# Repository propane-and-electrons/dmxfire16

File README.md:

dmxfire16
---------

The dmxfire16 is an Arduino-compatible 16 channel solid state relay board with built-in RS-485 serial. It is the wired version of the [wifire16](https://github.com/propane-and-electrons/wifire16) - much more information on the SSR side of the board is available there.

The RS-485 connection is DMX512 compatible with any number of Arduino libraries, so the dmxfire16 can be used to control LED strip lighting or flame effects with commercial off-the-shelf lighting controllers.

### Feature Summary

* Arduino compatible
  * Use "Duemilanove or Diecimila" as the Board in the Arduino IDE
* Programmable via 6-pin FTDI header or 6-pin ICSP header
* 16 DC load channels switched via MOSFET
* RS-485 support (DMX512 compatible) via 8P8C connectors
* Termination resistor and jumper for serial connection
* All ATMega I/O pins are broken out on the board
* DC load power is optoisolated from the control system power
* Power connectors use 5mm screw terminals or Anderson Powerpole connectors
* Load power status is reported to the microcontroller via an optoisolated input pin
* Output power channels are controlled with a TLC5940 constant current driver that works like a shift register
* Each output channel has a status LED for easy debugging
* TLC5940 control lines are broken out to input/output headers, so boards can be chained without additional control systems

### Documents

* [Schematic](docs/dmxfire16-schematic.pdf)
* [Bill of Materials](docs/dmxfire16-BOM.csv)

### DMX Details

* The [DMXSerial](http://www.mathertel.de/Arduino/DMXSerial.aspx) library can be used.
* **A** from the MAX-485 is positive signal, and goes to RJ-45 pin 1 / XLR pin 3.
* **B** from the MAX-485 is negative signal (aka signal invert), and goes to RJ-45 pin 2 / XLR pin 2.
* Many receivers implement `A-B` in hardware, so if these pins are swapped DMX _is unlikely to work_.

To send DMX data, `CTRLDE` (mapped to Arduino digital pin 6) must be set high:

```
  pinMode(6, OUTPUT);
  digitalWrite(6, HIGH);
```

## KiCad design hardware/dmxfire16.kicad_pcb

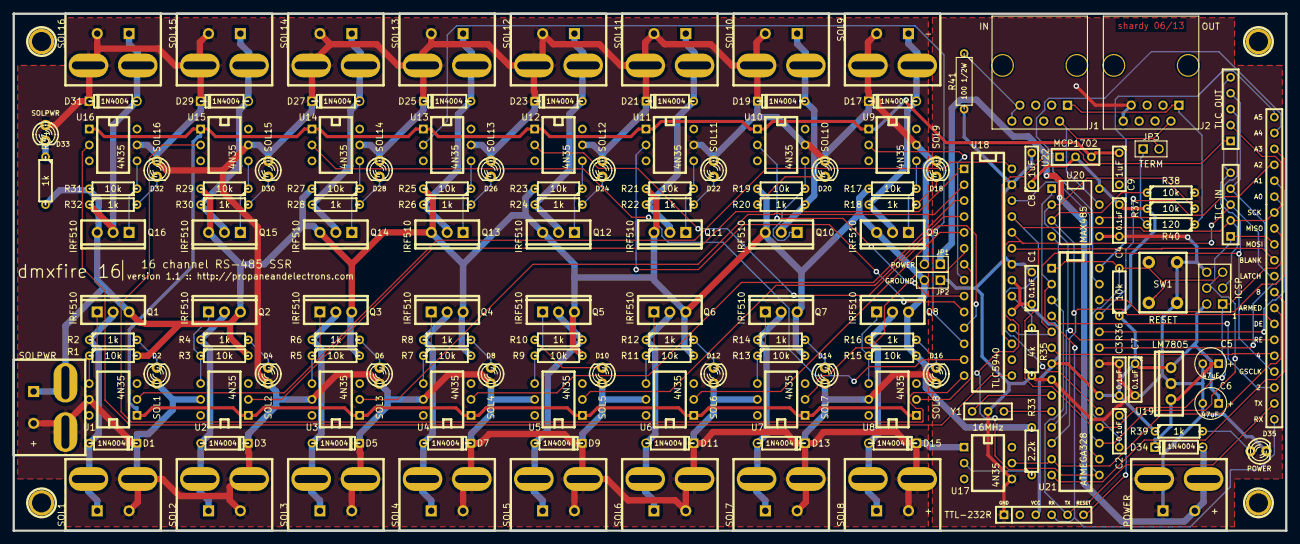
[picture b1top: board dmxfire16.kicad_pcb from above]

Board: 2 copper layers, 203.2 x 82.5 mm, 159 parts (0 on the bottom side), 104 nets.

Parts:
C1, C2, C3, C4, C7: 0.1uF; C2
C5, C6: 47uF; C1V5
C8, C9: 1uF; C2
D1, D3, D5, D7, D9, D11, D13, D15, D17, D19, D21, D23, D25, D27, D29, D31, D34: 1N4004; D3
D2: SOL1; LED-3MM
D4: SOL2; LED-3MM
D6: SOL3; LED-3MM
D8: SOL4; LED-3MM
D10: SOL5; LED-3MM
D12: SOL6; LED-3MM
D14: SOL7; LED-3MM
D16: SOL8; LED-3MM
D18: SOL9; LED-3MM
D20: SOL10; LED-3MM
D22: SOL11; LED-3MM
D24: SOL12; LED-3MM
D26: SOL13; LED-3MM
D28: SOL14; LED-3MM
D30: SOL15; LED-3MM
D32: SOL16; LED-3MM
D33: SOLPWR; LED-3MM
D35: POWER; LED-3MM
H1, H2, H3, H4: SCREWHOLE; 1pin
J1: IN; RJ45_8
J2: OUT; RJ45_8
JP1: POWER; PIN_ARRAY_2X1
JP2: GROUND; PIN_ARRAY_2X1
JP3: TERM; PIN_ARRAY_2X1
P1: SOL1; PP-2H-5MMSCREWTERM
P2: SOL2; PP-2H-5MMSCREWTERM
P3: SOL3; PP-2H-5MMSCREWTERM
P4: SOL4; PP-2H-5MMSCREWTERM
P5: SOL5; PP-2H-5MMSCREWTERM
P6: SOL6; PP-2H-5MMSCREWTERM
P7: SOL7; PP-2H-5MMSCREWTERM
P8: SOL8; PP-2H-5MMSCREWTERM
P9: SOL9; PP-2H-5MMSCREWTERM
P10: SOL10; PP-2H-5MMSCREWTERM
P11: SOL11; PP-2H-5MMSCREWTERM
P12: SOL12; PP-2H-5MMSCREWTERM
P13: SOL13; PP-2H-5MMSCREWTERM
P14: SOL14; PP-2H-5MMSCREWTERM
P15: SOL15; PP-2H-5MMSCREWTERM
P16: SOL16; PP-2H-5MMSCREWTERM
P17: SOLPWR; PP-2H-5MMSCREWTERM
P18: TLC IN; SIL-5
P19: TLC OUT; SIL-5
P20: TTL-232R; SIL-6
P21: ICSP; pin_array_3x2
P22: PORTC; SIL-6
P23: PORTD; SIL-8
P24: PORTB; SIL-6
P25: POWER; PP-2H-5MMSCREWTERM
Q1, Q2, Q3, Q4, Q5, Q6, Q7, Q8, Q9, Q10, Q11, Q12, Q13, Q14, Q15, Q16: IRF510; TO220GDS_VERT
R1, R3, R5, R7, R9, R11, R13, R15, R17, R19, R21, R23, R25, R27, R29, R31, R36, R37, R38: 10k; R3
R2, R4, R6, R8, R10, R12, R14, R16, R18, R20, R22, R24, R26, R28, R30, R32, R34, R39: 1k; R3
R33: 2.2k; R3
R35: 4k; R3
R40: 120; R3
R41: 100 1/2W; R3-5
SW1: RESET; SW-6MM
U1, U2, U3, U4, U5, U6, U7, U8, U9, U10, U11, U12, U13, U14, U15, U16, U17: 4N35; DIP-6__300
U18: TLC5940; DIP-28__300
U19: LM7805; 7805
U20: MAX485; DIP-8__300
U21: ATMEGA328; DIP-28__300
U22: MCP1702; SIL-3
Y1: 16MHz; SIL-3

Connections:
+1.5V: C9.1, U1.1, U2.1, U3.1, U4.1, U5.1, U6.1, U7.1, U8.1, U9.1, U10.1, U11.1, U12.1, U13.1, U14.1, U15.1, U16.1, U22.3
+12V: D34.1, JP1.1, P25.2
/ARMED: P23.8, U17.5, U21.13
/BLANK: P18.4, P19.4, P24.3, U18.23, U21.16
/CTRLDE: P23.7, R38.1, U20.3, U21.12
/CTRLRE: P23.6, R37.2, U20.2, U21.11
/GSCLK: P18.5, P19.5, P23.4, U18.18, U21.5
/MISO: P21.1, P24.5, U21.18
/MOSI: P18.1, P21.4, P24.4, U18.26, U21.17
/RESET: C2.2, P21.5, R36.2, SW1.1, SW1.2, U21.1
/RXD: P20.4, P23.1, U20.1, U21.2
/SCK: P18.2, P19.2, P21.3, P24.6, U18.25, U21.19
/SOL1: U1.2, U18.28
/SOL2: U2.2, U18.1
/SOL3: U3.2, U18.2
/SOL4: U4.2, U18.3
/SOL5: U5.2, U18.4
/SOL6: U6.2, U18.5
/SOL7: U7.2, U18.6
/SOL8: U8.2, U18.7
/SOL9: U9.2, U18.8
/SOL10: U10.2, U18.9
/SOL11: U11.2, U18.10
/SOL12: U12.2, U18.11
/SOL13: U13.2, U18.12
/SOL14: U14.2, U18.13
/SOL15: U15.2, U18.14
/SOL16: U16.2, U18.15
/SOLPWR+: D1.2, D2.1, D3.2, D4.1, D5.2, D6.1, D7.2, D8.1, D9.2, D10.1, D11.2, D12.1, D13.2, D14.1, D15.2, D16.1, D17.2, D18.1, D19.2, D20.1, D21.2, D22.1, D23.2, D24.1, D25.2, D26.1, D27.2, D28.1, D29.2, D30.1, D31.2, D32.1, D33.1, JP1.2, P1.2, P2.2, P3.2, P4.2, P5.2, P6.2, P7.2, P8.2, P9.2, P10.2, P11.2, P12.2, P13.2, P14.2, P15.2, P16.2, P17.2, U1.5, U2.5, U3.5, U4.5, U5.5, U6.5, U7.5, U8.5, U9.5, U10.5, U11.5, U12.5, U13.5, U14.5, U15.5, U16.5, U17.1
/SOLPWR-: JP2.2, P17.1, Q1.S, Q2.S, Q3.S, Q4.S, Q5.S, Q6.S, Q7.S, Q8.S, Q9.S, Q10.S, Q11.S, Q12.S, Q13.S, Q14.S, Q15.S, Q16.S, R1.2, R3.2, R5.2, R7.2, R9.2, R11.2, R13.2, R15.2, R17.2, R19.2, R21.2, R23.2, R25.2, R27.2, R29.2, R31.2, R33.2, R34.2
/SOUT: P19.1, U18.17
/TXD: P20.5, P23.2, U20.4, U21.3
/XLAT: P18.3, P19.3, P24.2, U18.24, U21.15
GND: C1.2, C3.2, C4.2, C5.2, C6.2, C7.2, C8.2, C9.2, D35.2, J2.7, J2.8, JP2.1, P20.1, P21.6, P25.1, R35.1, R38.2, R41.2, SW1.3, SW1.4, U17.4, U18.22, U18.27, U19.2, U20.5, U21.8, U21.22, U22.1, Y1.2
unnamed: C2.1, P20.6
unnamed: C5.1, D34.2, U19.1
unnamed: D1.1, P1.1, Q1.D, R2.1
unnamed: D2.2, R2.2
unnamed: D3.1, P2.1, Q2.D, R4.1
unnamed: D4.2, R4.2
unnamed: D5.1, P3.1, Q3.D, R6.1
unnamed: D6.2, R6.2
unnamed: D7.1, P4.1, Q4.D, R8.1
unnamed: D8.2, R8.2
unnamed: D9.1, P5.1, Q5.D, R10.1
unnamed: D10.2, R10.2
unnamed: D11.1, P6.1, Q6.D, R12.1
unnamed: D12.2, R12.2
unnamed: D13.1, P7.1, Q7.D, R14.1
unnamed: D14.2, R14.2
unnamed: D15.1, P8.1, Q8.D, R16.1
unnamed: D16.2, R16.2
unnamed: D17.1, P9.1, Q9.D, R18.1
unnamed: D18.2, R18.2
unnamed: D19.1, P10.1, Q10.D, R20.1
unnamed: D20.2, R20.2
unnamed: D21.1, P11.1, Q11.D, R22.1
unnamed: D22.2, R22.2
unnamed: D23.1, P12.1, Q12.D, R24.1
unnamed: D24.2, R24.2
unnamed: D25.1, P13.1, Q13.D, R26.1
unnamed: D26.2, R26.2
unnamed: D27.1, P14.1, Q14.D, R28.1
unnamed: D28.2, R28.2
unnamed: D29.1, P15.1, Q15.D, R30.1
unnamed: D30.2, R30.2
unnamed: D31.1, P16.1, Q16.D, R32.1
unnamed: D32.2, R32.2
unnamed: D33.2, R34.1
unnamed: D35.1, R39.2
unnamed: J1.1, J2.1, R40.1, U20.6
unnamed: J1.2, J2.2, JP3.2, U20.7
unnamed: J1.7, J1.8, R41.1
unnamed: JP3.1, R40.2
unnamed: P22.1, U21.23
unnamed: P22.2, U21.24
unnamed: P22.3, U21.25
unnamed: P22.4, U21.26
unnamed: P22.5, U21.27
unnamed: P22.6, U21.28
unnamed: P23.3, U21.4
unnamed: P23.5, U21.6
unnamed: P24.1, U21.14
unnamed: Q1.G, R1.1, U1.4
unnamed: Q2.G, R3.1, U2.4
unnamed: Q3.G, R5.1, U3.4
unnamed: Q4.G, R7.1, U4.4
unnamed: Q5.G, R9.1, U5.4
unnamed: Q6.G, R11.1, U6.4
unnamed: Q7.G, R13.1, U7.4
unnamed: Q8.G, R15.1, U8.4
unnamed: Q9.G, R17.1, U9.4
unnamed: Q10.G, R19.1, U10.4
unnamed: Q11.G, R21.1, U11.4
unnamed: Q12.G, R23.1, U12.4
unnamed: Q13.G, R25.1, U13.4
unnamed: Q14.G, R27.1, U14.4
unnamed: Q15.G, R29.1, U15.4
unnamed: Q16.G, R31.1, U16.4
unnamed: R33.1, U17.2
unnamed: R35.2, U18.20
unnamed: U21.9, Y1.1
unnamed: U21.10, Y1.3
VCC: C1.1, C3.1, C4.1, C6.1, C7.1, C8.1, P20.3, P21.2, R36.1, R37.1, R39.1, U18.19, U18.21, U19.3, U20.8, U21.7, U21.20, U22.2

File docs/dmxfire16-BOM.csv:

Designator,Package,Quantity,Part,Digi-Key Part
"C1,C2,C3,C4,C7",C2,5,0.1uF,490-5388-ND
"C5,C6",C1V5,2,47uF,P13464-ND
"C8,C9",C2,2,1uF,445-8614-ND
"D2,D4,D6,D8,D10,D12,D14,D16,D18,D20,D22,D24,D26,D28,D30,D32,D33,D35",LED-3MM,18,3mm LED,754-1606-ND
"D1,D3,D5,D7,D9,D11,D13,D15,D17,D19,D21,D23,D25,D27,D29,D31",D3,17,1N4004,641-1311-1-ND
"J1,J2",RJ45_8,2,8P8C,609-1046-ND
"JP1,JP2,JP3,P18,P19,P20","PIN_ARRAY_2X1, SIL-5,SIL-6",22,header pins,A34253-40-ND
"P1-P17,P25",PP-2H-5MMSCREWTERM,18,5mm screw terminal or Anderson Powerpole connector,ED2600-ND
P21,pin_array_3x2,3,2x header pins,A34344-40-ND
Q1-Q16,TO220GDS_VERT,16,IRF510,IRF510PBF-ND
"R1,R3,R5,R7,R9,R11,R13,R15,R17,R19,R21,R23,R25,R27,R29,R31,R36,R37,R38",R3,19,10k,10KQBK-ND
"R2,R4,R6,R8,R10,R12,R14,R16,R18,R20,R22,R24,R26,R28,R30,R32,R34,R39",R3,18,1k,1.0KQBK-ND
R33,R3,1,2.2k,2.2KQBK-ND
R35,R3,1,4k,not in stock?!
R40,R3,1,120,120QBK-ND
R41,R3-5,1,100 1/2W,100H-ND
SW1,SW-6MM,1,momentary pushbutton,SW400-ND
U1-U17,DIP-6__300,17,4N35,516-1557-5-ND
XU1-XU17,6-DIP socket,17,6DIP,A100203-ND
U18,DIP-28__300,1,TLC5940,296-17732-5-ND
U19,7805,1,LM7805,LM7805CT-ND
U20,DIP-8__300,1,SN75176,296-1739-5-ND
U21,DIP-28__300,1,ATMEGA328,ATMEGA328P-PU-ND
U22,SIL-3,1,"MCP1702 1V5",MCP1702-1502E/TO-ND
Y1,SIL-3,1,16MHz resonator,490-1214-ND

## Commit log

2013-03-12 initial checkin
2013-03-13 standardizing directory structure
2013-03-25 adding ignore file
2013-03-26 once again
2013-05-21 changing silk labels for RE and DE, kicad updating to mm?
2013-06-22 using pp/screw footprints, rebuilt all traces
2013-06-22 silkscreen fixup, putting signature on the copper
2013-06-22 changing npth to regular drills
2014-01-05 adding documentation
2014-01-05 slight readme mod
2014-01-21 changing atmega from IC1 to U21
2014-01-30 typo
2014-04-14 oops, fixed copypasta mistake from fenode
2015-03-14 adding 1V5 regulator for optoisolator LED power
2015-03-14 removing named pin
2015-03-18 slight silk change
2015-04-04 Add 1V5 regulator and related capacitors to BOM
2015-05-12 adding new parts to BOM
2015-05-12 clarification for regulator
2015-05-13 increasing zone clearance
2015-07-19 Adds substitute for discontinued part.
2018-04-04 Add note re: Board
    (Stop from having to bother Seth every time I forget this.)
2018-04-09 Add details on DMX sending
2018-04-09 Link to DMXSerial library.
